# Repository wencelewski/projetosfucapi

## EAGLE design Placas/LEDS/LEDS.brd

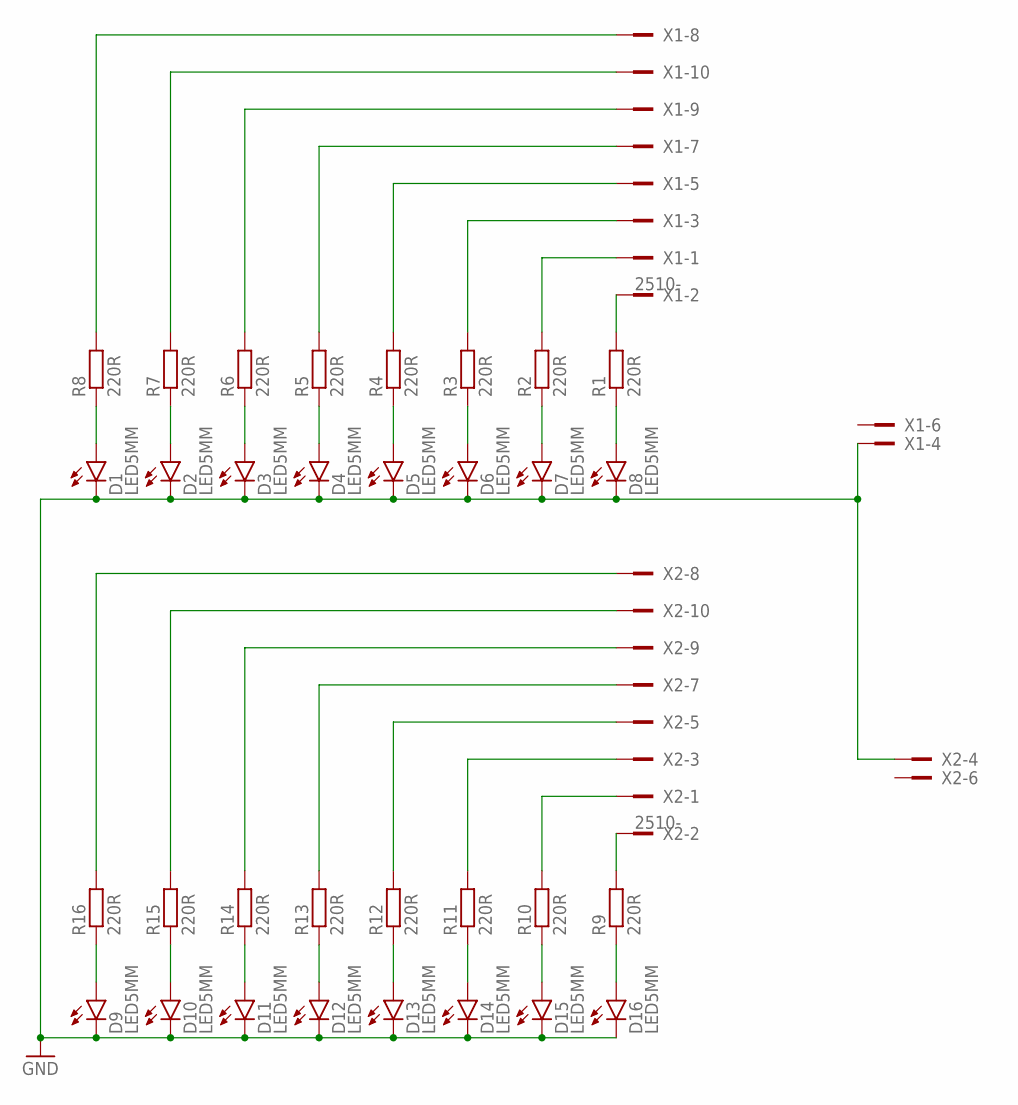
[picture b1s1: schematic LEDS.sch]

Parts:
D1, D2, D3, D4, D5, D6, D7, D8, D9, D10, D11, D12, D13, D14, D15, D16: LED5MM
R1, R2, R3, R4, R5, R6, R7, R8, R9, R10, R11, R12, R13, R14, R15, R16: 220R; 0204/ELVYS
X1, X2: 2510-; PAK100/2500-10

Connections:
GND: D1.K (C), D2.K (C), D3.K (C), D4.K (C), D5.K (C), D6.K (C), D7.K (C), D8.K (C), D9.K (C), D10.K (C), D11.K (C), D12.K (C), D13.K (C), D14.K (C), D15.K (C), D16.K (C), X1.4, X2.4
unnamed: R16.P$2 (2), X2.8
unnamed: R8.P$2 (2), X1.8
unnamed: R6.P$2 (2), X1.9
unnamed: R7.P$2 (2), X1.10
unnamed: R5.P$2 (2), X1.7
unnamed: R4.P$2 (2), X1.5
unnamed: R3.P$2 (2), X1.3
unnamed: R2.P$2 (2), X1.1
unnamed: R1.P$2 (2), X1.2
unnamed: R15.P$2 (2), X2.10
unnamed: R14.P$2 (2), X2.9
unnamed: R13.P$2 (2), X2.7
unnamed: R12.P$2 (2), X2.5
unnamed: R11.P$2 (2), X2.3
unnamed: R10.P$2 (2), X2.1
unnamed: R9.P$2 (2), X2.2
unnamed: D1.A, R8.P$1 (1)
unnamed: D2.A, R7.P$1 (1)
unnamed: D3.A, R6.P$1 (1)
unnamed: D4.A, R5.P$1 (1)
unnamed: D5.A, R4.P$1 (1)
unnamed: D6.A, R3.P$1 (1)
unnamed: D7.A, R2.P$1 (1)
unnamed: D8.A, R1.P$1 (1)
unnamed: D9.A, R16.P$1 (1)
unnamed: D10.A, R15.P$1 (1)
unnamed: D11.A, R14.P$1 (1)
unnamed: D12.A, R13.P$1 (1)
unnamed: D13.A, R12.P$1 (1)
unnamed: D14.A, R11.P$1 (1)
unnamed: D15.A, R10.P$1 (1)
unnamed: D16.A, R9.P$1 (1)

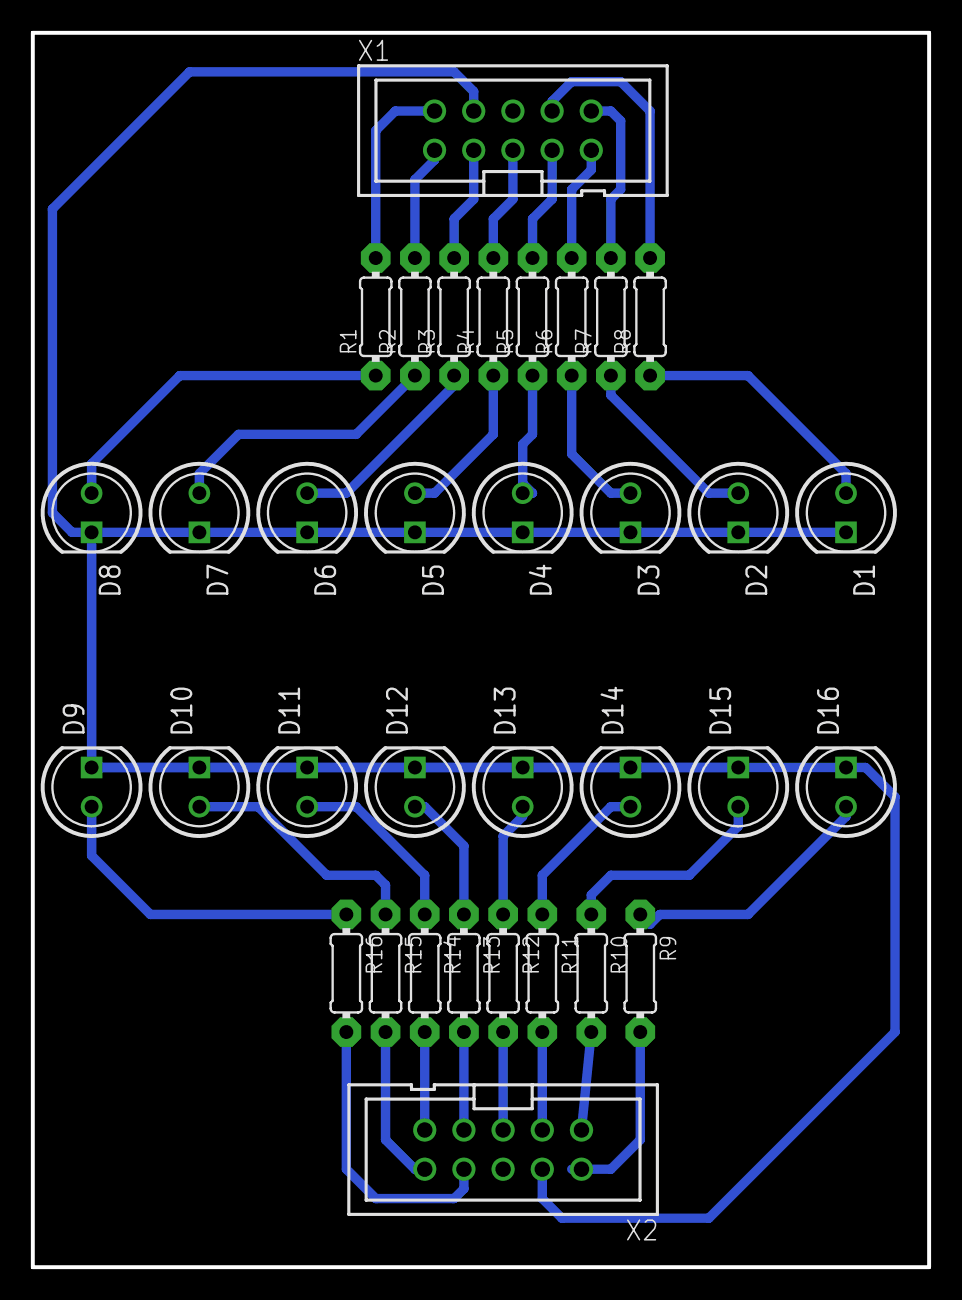
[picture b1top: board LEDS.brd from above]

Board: 2 copper layers, 58.1 x 80.0 mm, 34 parts (0 on the bottom side), 33 nets.

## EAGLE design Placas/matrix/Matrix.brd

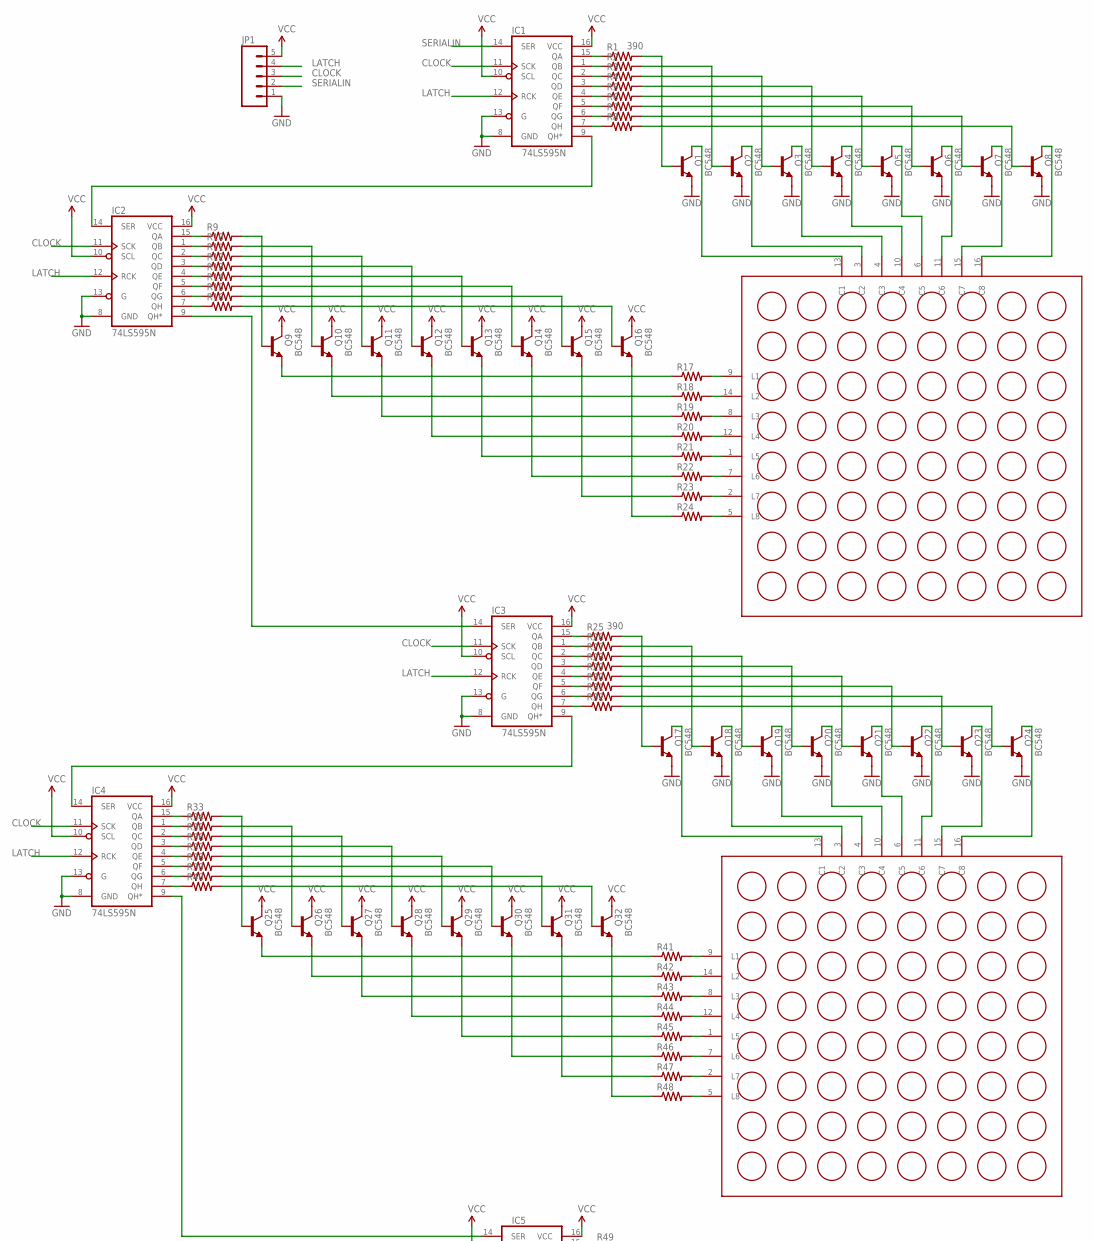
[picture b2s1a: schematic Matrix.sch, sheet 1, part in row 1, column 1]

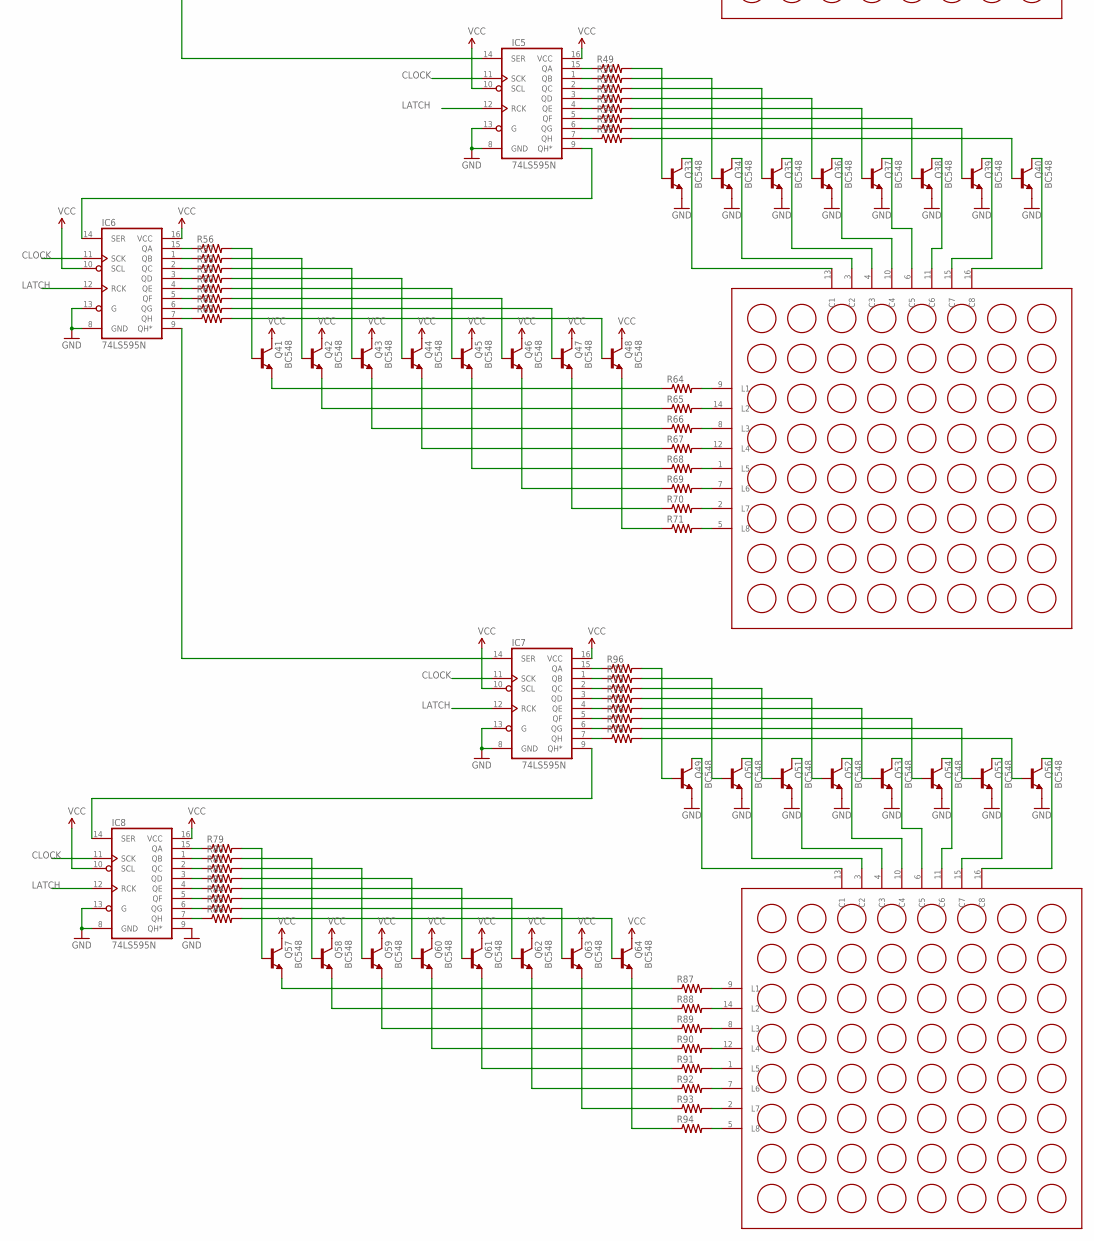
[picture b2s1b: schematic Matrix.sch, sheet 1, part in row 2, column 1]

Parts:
IC1, IC2, IC3, IC4, IC5, IC6, IC7, IC8: 74LS595N; DIL16
JP1: M05PTH_LONGPADS; 1X05_LONGPADS
Q1, Q2, Q3, Q4, Q5, Q6, Q7, Q8, Q9, Q10, Q11, Q12, Q13, Q14, Q15, Q16, Q17, Q18, Q19, Q20, Q21, Q22, Q23, Q24, Q25, Q26, Q27, Q28, Q29, Q30, Q31, Q32, Q33, Q34, Q35, Q36, Q37, Q38, Q39, Q40, Q41, Q42, Q43, Q44, Q45, Q46, Q47, Q48, Q49, Q50, Q51, Q52, Q53, Q54, Q55, Q56, Q57, Q58, Q59, Q60, Q61, Q62, Q63, Q64: BC548; TO92-EBC
R1, R2, R3, R4, R5, R6, R7, R8, R9, R10, R11, R12, R13, R14, R15, R16, R17, R18, R19, R20, R21, R22, R23, R24, R25, R26, R27, R28, R29, R30, R31, R32, R33, R34, R35, R36, R37, R38, R39, R40, R41, R42, R43, R44, R45, R46, R47, R48, R49, R50, R51, R52, R53, R54, R55, R56, R57, R58, R59, R60, R61, R62, R63, R64, R65, R66, R67, R68, R69, R70, R71, R72, R73, R74, R75, R76, R77, R78, R79, R80, R81, R82, R83, R84, R85, R86, R87, R88, R89, R90, R91, R92, R93, R94, R95, R96: 390; AXIAL-0.4
U$1, U$2, U$3, U$4: LEDMATRIX(HS2388); HS2388

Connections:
CLOCK: IC1.11 (SCK), IC2.11 (SCK), IC3.11 (SCK), IC4.11 (SCK), IC5.11 (SCK), IC6.11 (SCK), IC7.11 (SCK), IC8.11 (SCK), JP1.3
GND: IC1.8 (GND), IC1.13 (G), IC2.8 (GND), IC2.13 (G), IC3.8 (GND), IC3.13 (G), IC4.8 (GND), IC4.13 (G), IC5.8 (GND), IC5.13 (G), IC6.8 (GND), IC6.13 (G), IC7.8 (GND), IC7.13 (G), IC8.8 (GND), IC8.9 (QH*), IC8.13 (G), JP1.1, Q1.E, Q2.E, Q3.E, Q4.E, Q5.E, Q6.E, Q7.E, Q8.E, Q17.E, Q18.E, Q19.E, Q20.E, Q21.E, Q22.E, Q23.E, Q24.E, Q33.E, Q34.E, Q35.E, Q36.E, Q37.E, Q38.E, Q39.E, Q40.E, Q49.E, Q50.E, Q51.E, Q52.E, Q53.E, Q54.E, Q55.E, Q56.E
LATCH: IC1.12 (RCK), IC2.12 (RCK), IC3.12 (RCK), IC4.12 (RCK), IC5.12 (RCK), IC6.12 (RCK), IC7.12 (RCK), IC8.12 (RCK), JP1.4
unnamed: Q1.B, R1.P$2 (2)
unnamed: IC1.15 (QA), R1.P$1 (1)
unnamed: Q8.B, R8.P$2 (2)
unnamed: IC1.1 (QB), R2.P$1 (1)
unnamed: Q16.E, R24.P$1 (1)
unnamed: Q15.E, R23.P$1 (1)
unnamed: Q14.E, R22.P$1 (1)
unnamed: IC1.2 (QC), R3.P$1 (1)
unnamed: IC1.3 (QD), R4.P$1 (1)
unnamed: IC1.4 (QE), R5.P$1 (1)
unnamed: IC1.5 (QF), R6.P$1 (1)
unnamed: IC1.6 (QG), R7.P$1 (1)
unnamed: IC1.7 (QH), R8.P$1 (1)
unnamed: Q13.E, R21.P$1 (1)
unnamed: Q2.B, R2.P$2 (2)
unnamed: Q4.B, R4.P$2 (2)
unnamed: Q5.B, R5.P$2 (2)
unnamed: Q6.B, R6.P$2 (2)
unnamed: Q7.B, R7.P$2 (2)
unnamed: Q1.C, U$1.13 (C1)
unnamed: Q2.C, U$1.3 (C2)
unnamed: Q3.B, R3.P$2 (2)
unnamed: Q24.B, R32.P$2 (2)
unnamed: Q4.C, U$1.10 (C4)
unnamed: Q5.C, U$1.6 (C5)
unnamed: Q6.C, U$1.11 (C6)
unnamed: Q7.C, U$1.15 (C7)
unnamed: Q8.C, U$1.16 (C8)
unnamed: Q12.E, R20.P$1 (1)
unnamed: Q11.E, R19.P$1 (1)
unnamed: Q10.E, R18.P$1 (1)
unnamed: Q9.E, R17.P$1 (1)
unnamed: R17.P$2 (2), U$1.9 (L1)
unnamed: R18.P$2 (2), U$1.14 (L2)
unnamed: R19.P$2 (2), U$1.8 (L3)
unnamed: R20.P$2 (2), U$1.12 (L4)
unnamed: R21.P$2 (2), U$1.1 (L5)
unnamed: R22.P$2 (2), U$1.7 (L6)
unnamed: R23.P$2 (2), U$1.2 (L7)
unnamed: R24.P$2 (2), U$1.5 (L8)
unnamed: Q9.B, R9.P$2 (2)
unnamed: Q10.B, R10.P$2 (2)
unnamed: Q11.B, R11.P$2 (2)
unnamed: Q12.B, R12.P$2 (2)
unnamed: Q13.B, R13.P$2 (2)
unnamed: Q14.B, R14.P$2 (2)
unnamed: Q15.B, R15.P$2 (2)
unnamed: Q16.B, R16.P$2 (2)
unnamed: IC2.15 (QA), R9.P$1 (1)
unnamed: IC2.1 (QB), R10.P$1 (1)
unnamed: IC2.2 (QC), R11.P$1 (1)
unnamed: IC2.3 (QD), R12.P$1 (1)
unnamed: IC2.4 (QE), R13.P$1 (1)
unnamed: IC2.5 (QF), R14.P$1 (1)
unnamed: IC2.6 (QG), R15.P$1 (1)
unnamed: IC2.7 (QH), R16.P$1 (1)
unnamed: IC1.9 (QH*), IC2.14 (SER)
unnamed: Q19.B, R27.P$2 (2)
unnamed: Q3.C, U$1.4 (C3)
unnamed: Q17.B, R25.P$2 (2)
unnamed: Q18.B, R26.P$2 (2)
unnamed: Q20.B, R28.P$2 (2)
unnamed: Q21.B, R29.P$2 (2)
unnamed: Q22.B, R30.P$2 (2)
unnamed: Q23.B, R31.P$2 (2)
unnamed: Q17.C, U$2.13 (C1)
unnamed: Q18.C, U$2.3 (C2)
unnamed: Q20.C, U$2.10 (C4)
unnamed: Q21.C, U$2.6 (C5)
unnamed: Q22.C, U$2.11 (C6)
unnamed: Q23.C, U$2.15 (C7)
unnamed: Q24.C, U$2.16 (C8)
unnamed: IC3.15 (QA), R25.P$1 (1)
unnamed: IC3.1 (QB), R26.P$1 (1)
unnamed: IC3.2 (QC), R27.P$1 (1)
unnamed: IC3.3 (QD), R28.P$1 (1)
unnamed: IC3.4 (QE), R29.P$1 (1)
unnamed: IC3.5 (QF), R30.P$1 (1)
unnamed: IC3.6 (QG), R31.P$1 (1)
unnamed: IC3.7 (QH), R32.P$1 (1)
unnamed: Q32.E, R48.P$1 (1)
unnamed: Q31.E, R47.P$1 (1)
unnamed: Q30.E, R46.P$1 (1)
unnamed: Q29.E, R45.P$1 (1)
unnamed: Q28.E, R44.P$1 (1)
unnamed: Q27.E, R43.P$1 (1)
unnamed: Q26.E, R42.P$1 (1)
unnamed: Q25.E, R41.P$1 (1)
unnamed: R41.P$2 (2), U$2.9 (L1)
unnamed: R42.P$2 (2), U$2.14 (L2)
unnamed: R43.P$2 (2), U$2.8 (L3)
unnamed: R44.P$2 (2), U$2.12 (L4)
unnamed: R45.P$2 (2), U$2.1 (L5)
unnamed: R46.P$2 (2), U$2.7 (L6)
unnamed: R47.P$2 (2), U$2.2 (L7)
unnamed: R48.P$2 (2), U$2.5 (L8)
unnamed: Q25.B, R33.P$2 (2)
unnamed: Q26.B, R34.P$2 (2)
unnamed: Q27.B, R35.P$2 (2)
unnamed: Q28.B, R36.P$2 (2)
unnamed: Q29.B, R37.P$2 (2)
unnamed: Q30.B, R38.P$2 (2)
unnamed: Q31.B, R39.P$2 (2)
unnamed: Q32.B, R40.P$2 (2)
unnamed: IC4.15 (QA), R33.P$1 (1)
unnamed: IC4.1 (QB), R34.P$1 (1)
unnamed: IC4.2 (QC), R35.P$1 (1)
unnamed: IC4.3 (QD), R36.P$1 (1)
unnamed: IC4.4 (QE), R37.P$1 (1)
unnamed: IC4.5 (QF), R38.P$1 (1)
unnamed: IC4.6 (QG), R39.P$1 (1)
unnamed: IC4.7 (QH), R40.P$1 (1)
unnamed: Q19.C, U$2.4 (C3)
unnamed: IC3.9 (QH*), IC4.14 (SER)
unnamed: Q40.B, R95.P$2 (2)
unnamed: Q35.B, R51.P$2 (2)
unnamed: IC2.9 (QH*), IC3.14 (SER)
unnamed: Q34.B, R50.P$2 (2)
unnamed: Q36.B, R52.P$2 (2)
unnamed: Q37.B, R53.P$2 (2)
unnamed: Q38.B, R54.P$2 (2)
unnamed: Q39.B, R55.P$2 (2)
unnamed: Q33.C, U$3.13 (C1)
unnamed: Q34.C, U$3.3 (C2)
unnamed: Q36.C, U$3.10 (C4)
unnamed: Q37.C, U$3.6 (C5)
unnamed: Q38.C, U$3.11 (C6)
unnamed: Q39.C, U$3.15 (C7)
unnamed: Q40.C, U$3.16 (C8)
unnamed: Q33.B, R49.P$2 (2)
unnamed: IC6.9 (QH*), IC7.14 (SER)
unnamed: IC5.7 (QH), R95.P$1 (1)
unnamed: IC5.6 (QG), R55.P$1 (1)
unnamed: IC5.5 (QF), R54.P$1 (1)
unnamed: IC5.4 (QE), R53.P$1 (1)
unnamed: IC5.3 (QD), R52.P$1 (1)
unnamed: Q48.E, R71.P$1 (1)
unnamed: Q47.E, R70.P$1 (1)
unnamed: Q46.E, R69.P$1 (1)
unnamed: Q45.E, R68.P$1 (1)
unnamed: Q44.E, R67.P$1 (1)
unnamed: Q43.E, R66.P$1 (1)
unnamed: Q42.E, R65.P$1 (1)
unnamed: Q41.E, R64.P$1 (1)
unnamed: R64.P$2 (2), U$3.9 (L1)
unnamed: R65.P$2 (2), U$3.14 (L2)
unnamed: R66.P$2 (2), U$3.8 (L3)
unnamed: R67.P$2 (2), U$3.12 (L4)
unnamed: R68.P$2 (2), U$3.1 (L5)
unnamed: R69.P$2 (2), U$3.7 (L6)
unnamed: R70.P$2 (2), U$3.2 (L7)
unnamed: R71.P$2 (2), U$3.5 (L8)
unnamed: Q41.B, R56.P$2 (2)
unnamed: Q42.B, R57.P$2 (2)
unnamed: Q43.B, R58.P$2 (2)
unnamed: Q44.B, R59.P$2 (2)
unnamed: Q45.B, R60.P$2 (2)
unnamed: Q46.B, R61.P$2 (2)
unnamed: Q47.B, R62.P$2 (2)
unnamed: Q48.B, R63.P$2 (2)
unnamed: IC6.15 (QA), R56.P$1 (1)
unnamed: IC6.1 (QB), R57.P$1 (1)
unnamed: IC6.2 (QC), R58.P$1 (1)
unnamed: IC6.3 (QD), R59.P$1 (1)
unnamed: IC6.4 (QE), R60.P$1 (1)
unnamed: IC6.5 (QF), R61.P$1 (1)
unnamed: IC6.6 (QG), R62.P$1 (1)
unnamed: IC6.7 (QH), R63.P$1 (1)
unnamed: Q35.C, U$3.4 (C3)
unnamed: IC5.9 (QH*), IC6.14 (SER)
unnamed: Q56.B, R78.P$2 (2)
unnamed: Q51.B, R73.P$2 (2)
unnamed: Q49.B, R96.P$2 (2)
unnamed: Q50.B, R72.P$2 (2)
unnamed: Q52.B, R74.P$2 (2)
unnamed: Q53.B, R75.P$2 (2)
unnamed: Q54.B, R76.P$2 (2)
unnamed: Q55.B, R77.P$2 (2)
unnamed: Q49.C, U$4.13 (C1)
unnamed: Q50.C, U$4.3 (C2)
unnamed: Q52.C, U$4.10 (C4)
unnamed: Q53.C, U$4.6 (C5)
unnamed: Q54.C, U$4.11 (C6)
unnamed: Q55.C, U$4.15 (C7)
unnamed: Q56.C, U$4.16 (C8)
unnamed: IC7.1 (QB), R72.P$1 (1)
unnamed: IC7.2 (QC), R73.P$1 (1)
unnamed: IC7.3 (QD), R74.P$1 (1)
unnamed: IC7.4 (QE), R75.P$1 (1)
unnamed: IC7.5 (QF), R76.P$1 (1)
unnamed: IC7.6 (QG), R77.P$1 (1)
unnamed: IC7.7 (QH), R78.P$1 (1)
unnamed: Q64.E, R94.P$1 (1)
unnamed: Q63.E, R93.P$1 (1)
unnamed: Q62.E, R92.P$1 (1)
unnamed: Q61.E, R91.P$1 (1)
unnamed: Q60.E, R90.P$1 (1)
unnamed: Q59.E, R89.P$1 (1)
unnamed: Q58.E, R88.P$1 (1)
unnamed: Q57.E, R87.P$1 (1)
unnamed: R87.P$2 (2), U$4.9 (L1)
unnamed: R88.P$2 (2), U$4.14 (L2)
unnamed: R89.P$2 (2), U$4.8 (L3)
unnamed: R90.P$2 (2), U$4.12 (L4)
unnamed: R91.P$2 (2), U$4.1 (L5)
unnamed: R92.P$2 (2), U$4.7 (L6)
unnamed: R93.P$2 (2), U$4.2 (L7)
unnamed: R94.P$2 (2), U$4.5 (L8)
unnamed: Q57.B, R79.P$2 (2)
unnamed: Q58.B, R80.P$2 (2)
unnamed: Q59.B, R81.P$2 (2)
unnamed: Q60.B, R82.P$2 (2)
unnamed: Q61.B, R83.P$2 (2)
unnamed: Q62.B, R84.P$2 (2)
unnamed: Q63.B, R85.P$2 (2)
unnamed: Q64.B, R86.P$2 (2)
unnamed: IC8.15 (QA), R79.P$1 (1)
unnamed: IC8.1 (QB), R80.P$1 (1)
unnamed: IC8.2 (QC), R81.P$1 (1)
unnamed: IC8.3 (QD), R82.P$1 (1)
unnamed: IC8.4 (QE), R83.P$1 (1)
unnamed: IC8.5 (QF), R84.P$1 (1)
unnamed: IC8.6 (QG), R85.P$1 (1)
unnamed: IC8.7 (QH), R86.P$1 (1)
unnamed: Q51.C, U$4.4 (C3)
unnamed: IC7.9 (QH*), IC8.14 (SER)
unnamed: IC4.9 (QH*), IC5.14 (SER)
unnamed: IC5.2 (QC), R51.P$1 (1)
unnamed: IC5.1 (QB), R50.P$1 (1)
unnamed: IC5.15 (QA), R49.P$1 (1)
unnamed: IC7.15 (QA), R96.P$1 (1)
SERIALIN: IC1.14 (SER), JP1.2
VCC: IC1.10 (SCL), IC1.16 (VCC), IC2.10 (SCL), IC2.16 (VCC), IC3.10 (SCL), IC3.16 (VCC), IC4.10 (SCL), IC4.16 (VCC), IC5.10 (SCL), IC5.16 (VCC), IC6.10 (SCL), IC6.16 (VCC), IC7.10 (SCL), IC7.16 (VCC), IC8.10 (SCL), IC8.16 (VCC), JP1.5, Q9.C, Q10.C, Q11.C, Q12.C, Q13.C, Q14.C, Q15.C, Q16.C, Q25.C, Q26.C, Q27.C, Q28.C, Q29.C, Q30.C, Q31.C, Q32.C, Q41.C, Q42.C, Q43.C, Q44.C, Q45.C, Q46.C, Q47.C, Q48.C, Q57.C, Q58.C, Q59.C, Q60.C, Q61.C, Q62.C, Q63.C, Q64.C

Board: 2 copper layers, 173 parts (0 on the bottom side), 236 nets, no tracks yet.

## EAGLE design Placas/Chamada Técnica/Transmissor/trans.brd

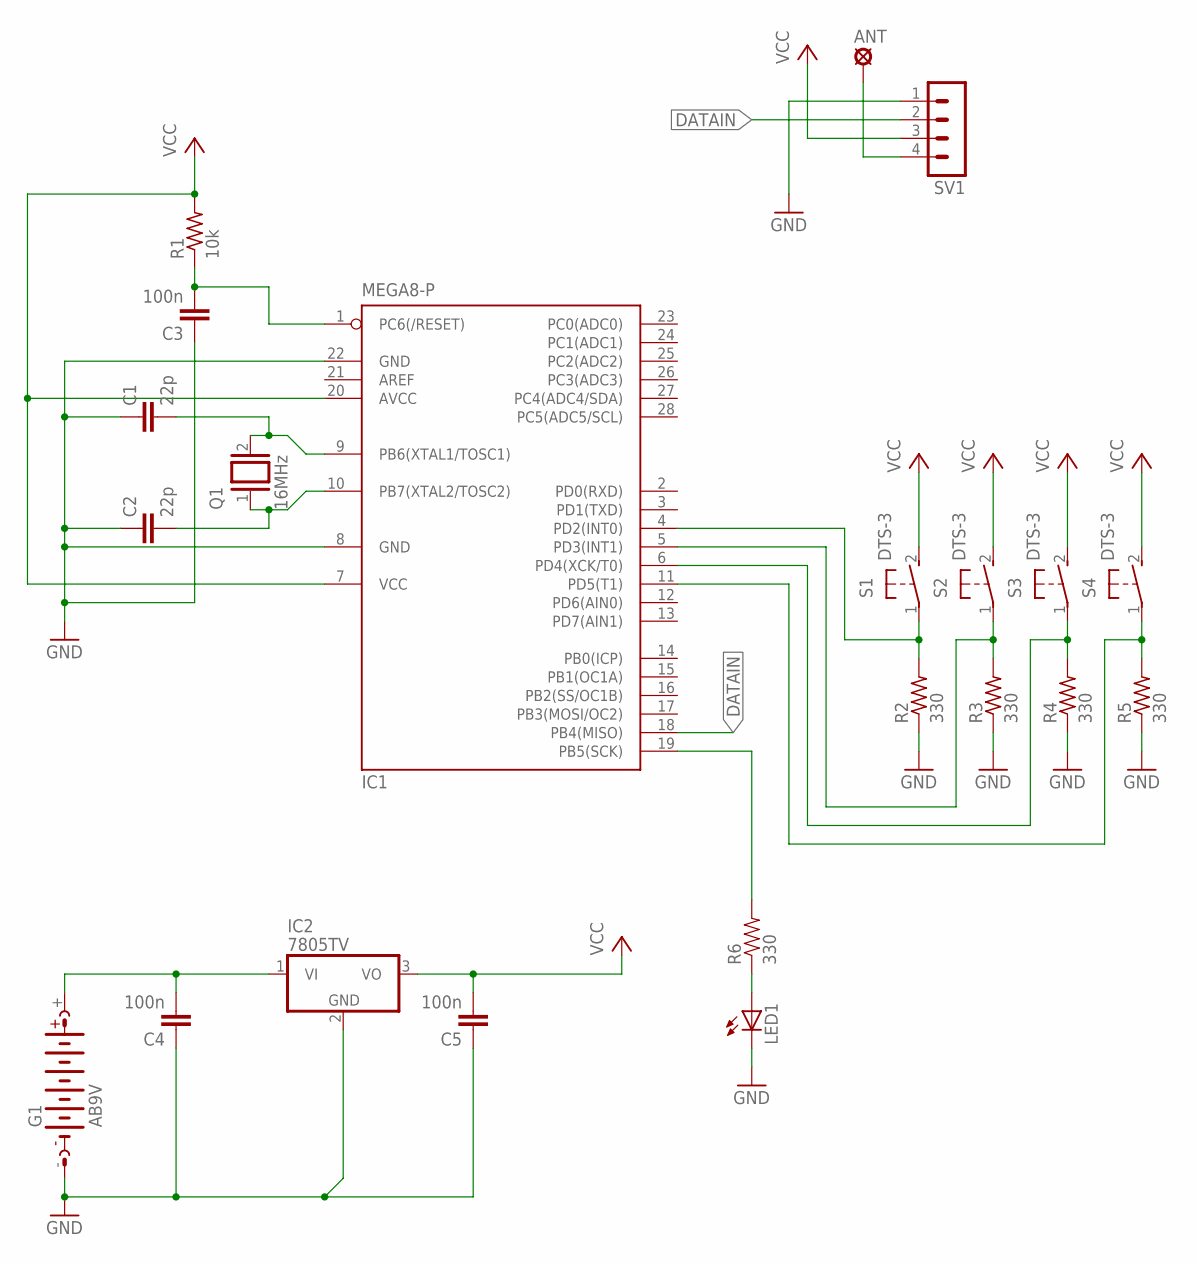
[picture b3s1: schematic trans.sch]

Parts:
ANT: LSP10
C1, C2: 22p; C025-024X044
C3, C4, C5: 100n; C025-024X044
G1: AB9V
IC1: MEGA8-P; DIL28-3
IC2: 7805TV; TO220V
LED1: LED5MM
Q1: 16MHz; QS
R1: 10k; 0204V
R2, R3, R4, R5: 330; 0204V
R6: 330; AXIAL-0.4
S1, S2, S3, S4: DTS-3
SV1: MA04-1

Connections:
DATAIN: IC1.18 (PB4(MISO)), SV1.2
GND: C1.1, C2.1, C3.1, C4.1, C5.1, G1.-, IC1.8 (GND), IC1.22 (GND), IC2.2 (GND), LED1.K (C), R2.1, R3.1, R4.1, R5.1, SV1.1
unnamed: C1.2, IC1.9 (PB6(XTAL1/TOSC1)), Q1.2
unnamed: C2.2, IC1.10 (PB7(XTAL2/TOSC2)), Q1.1
unnamed: C3.2, IC1.1 (PC6(/RESET)), R1.1
unnamed: ANT.MP, SV1.4
unnamed: C4.2, G1.+, IC2.1 (VI)
unnamed: IC1.4 (PD2(INT0)), R2.2, S1.1
unnamed: IC1.5 (PD3(INT1)), R3.2, S2.1
unnamed: IC1.19 (PB5(SCK)), R6.P$2 (2)
unnamed: IC1.11 (PD5(T1)), R5.2, S4.1
unnamed: IC1.6 (PD4(XCK/T0)), R4.2, S3.1
unnamed: LED1.A, R6.P$1 (1)
VCC: C5.2, IC1.7 (VCC), IC1.20 (AVCC), IC2.3 (VO), R1.2, S1.2, S2.2, S3.2, S4.2, SV1.3

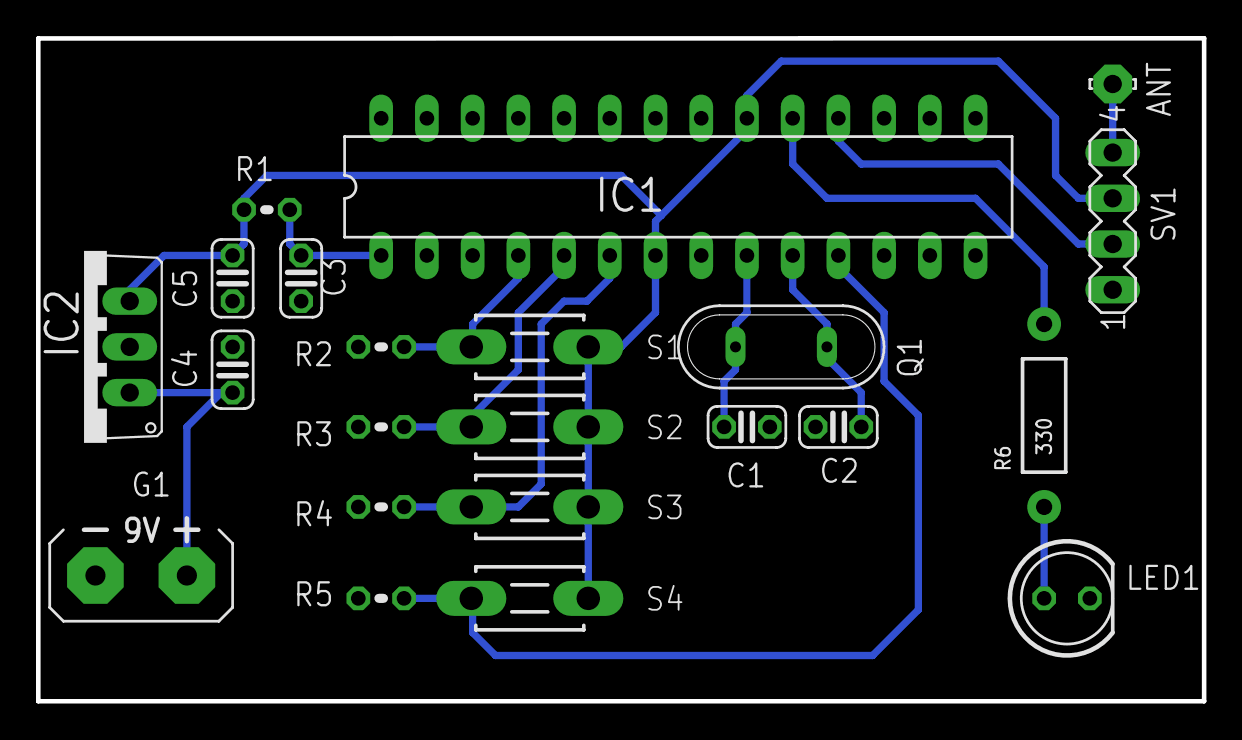
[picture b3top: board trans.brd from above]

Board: 2 copper layers, 64.8 x 36.8 mm, 22 parts (0 on the bottom side), 14 nets.

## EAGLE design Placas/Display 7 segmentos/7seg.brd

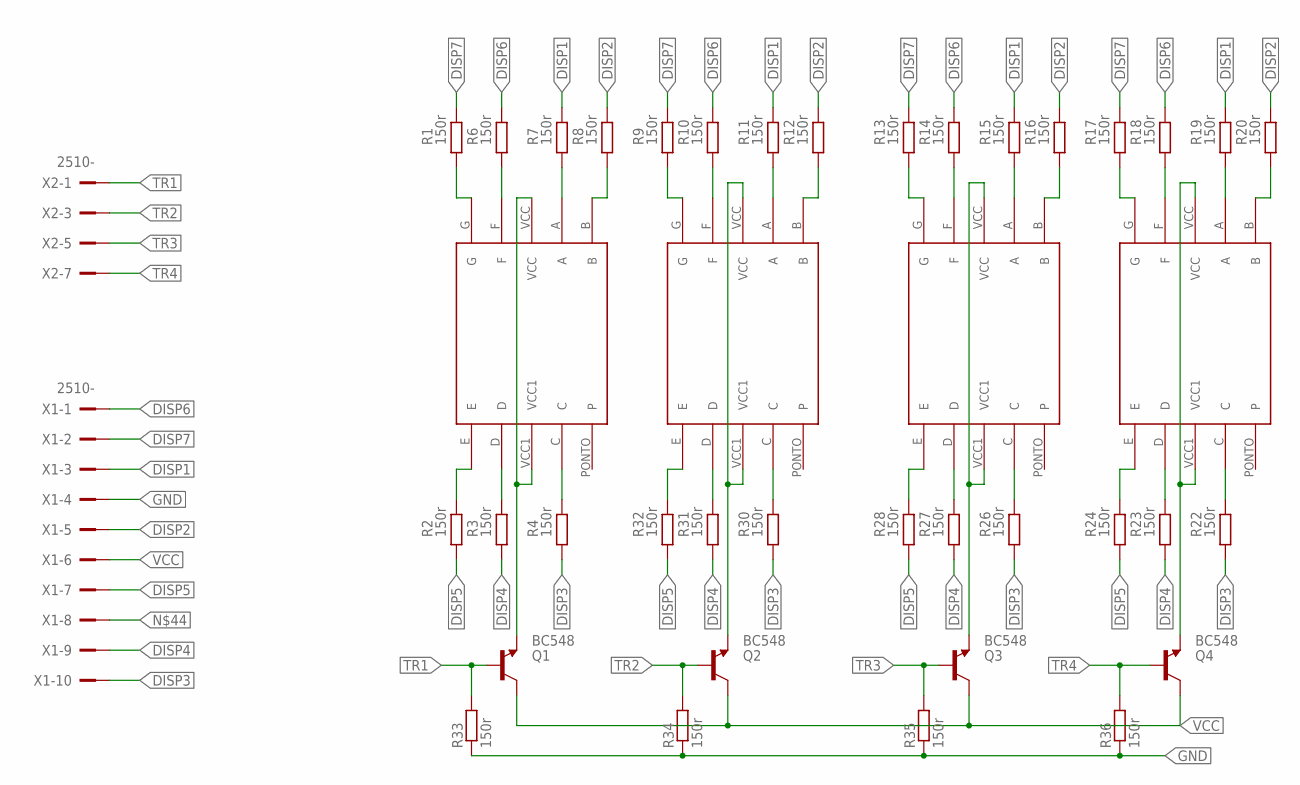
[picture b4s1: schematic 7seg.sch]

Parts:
Q1, Q2, Q3, Q4: BC548; TO92-EBC
R1, R2, R3, R4, R6, R7, R8, R9, R10, R11, R12, R13, R14, R15, R16, R17, R18, R19, R20, R22, R23, R24, R26, R27, R28, R30, R31, R32, R33, R34, R35, R36: 150r; 0204/ELVYS
U$1, U$2, U$3, U$4: HS-12101BS
X1, X2: 2510-; PAK100/2500-10

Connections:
DISP1: R7.P$2 (2), R11.P$2 (2), R15.P$2 (2), R19.P$2 (2), X1.3
DISP2: R8.P$2 (2), R12.P$2 (2), R16.P$2 (2), R20.P$2 (2), X1.5
DISP3: R4.P$1 (1), R22.P$1 (1), R26.P$1 (1), R30.P$1 (1), X1.10
DISP4: R3.P$1 (1), R23.P$1 (1), R27.P$1 (1), R31.P$1 (1), X1.9
DISP5: R2.P$1 (1), R24.P$1 (1), R28.P$1 (1), R32.P$1 (1), X1.7
DISP6: R6.P$2 (2), R10.P$2 (2), R14.P$2 (2), R18.P$2 (2), X1.1
DISP7: R1.P$2 (2), R9.P$2 (2), R13.P$2 (2), R17.P$2 (2), X1.2
GND: R33.P$1 (1), R34.P$1 (1), R35.P$1 (1), R36.P$1 (1), X1.4
unnamed: Q1.E, U$1.VCC, U$1.VCC1
unnamed: Q2.E, U$2.VCC, U$2.VCC1
unnamed: R1.P$1 (1), U$1.G
unnamed: R2.P$2 (2), U$1.E
unnamed: R4.P$2 (2), U$1.C
unnamed: R3.P$2 (2), U$1.D
unnamed: R6.P$1 (1), U$1.F
unnamed: R7.P$1 (1), U$1.A
unnamed: R8.P$1 (1), U$1.B
unnamed: R9.P$1 (1), U$2.G
unnamed: R10.P$1 (1), U$2.F
unnamed: R11.P$1 (1), U$2.A
unnamed: R12.P$1 (1), U$2.B
unnamed: R13.P$1 (1), U$3.G
unnamed: R14.P$1 (1), U$3.F
unnamed: R15.P$1 (1), U$3.A
unnamed: R16.P$1 (1), U$3.B
unnamed: R17.P$1 (1), U$4.G
unnamed: R18.P$1 (1), U$4.F
unnamed: R19.P$1 (1), U$4.A
unnamed: R20.P$1 (1), U$4.B
unnamed: R22.P$2 (2), U$4.C
unnamed: R23.P$2 (2), U$4.D
unnamed: R24.P$2 (2), U$4.E
unnamed: R26.P$2 (2), U$3.C
unnamed: R27.P$2 (2), U$3.D
unnamed: R28.P$2 (2), U$3.E
unnamed: R30.P$2 (2), U$2.C
unnamed: R31.P$2 (2), U$2.D
unnamed: R32.P$2 (2), U$2.E
unnamed: Q4.E, U$4.VCC, U$4.VCC1
unnamed: Q3.E, U$3.VCC, U$3.VCC1
TR1: Q1.B, R33.P$2 (2), X2.1
TR2: Q2.B, R34.P$2 (2), X2.3
TR3: Q3.B, R35.P$2 (2), X2.5
TR4: Q4.B, R36.P$2 (2), X2.7
VCC: Q1.C, Q2.C, Q3.C, Q4.C, X1.6

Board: 2 copper layers, 42 parts (0 on the bottom side), 45 nets, no tracks yet.

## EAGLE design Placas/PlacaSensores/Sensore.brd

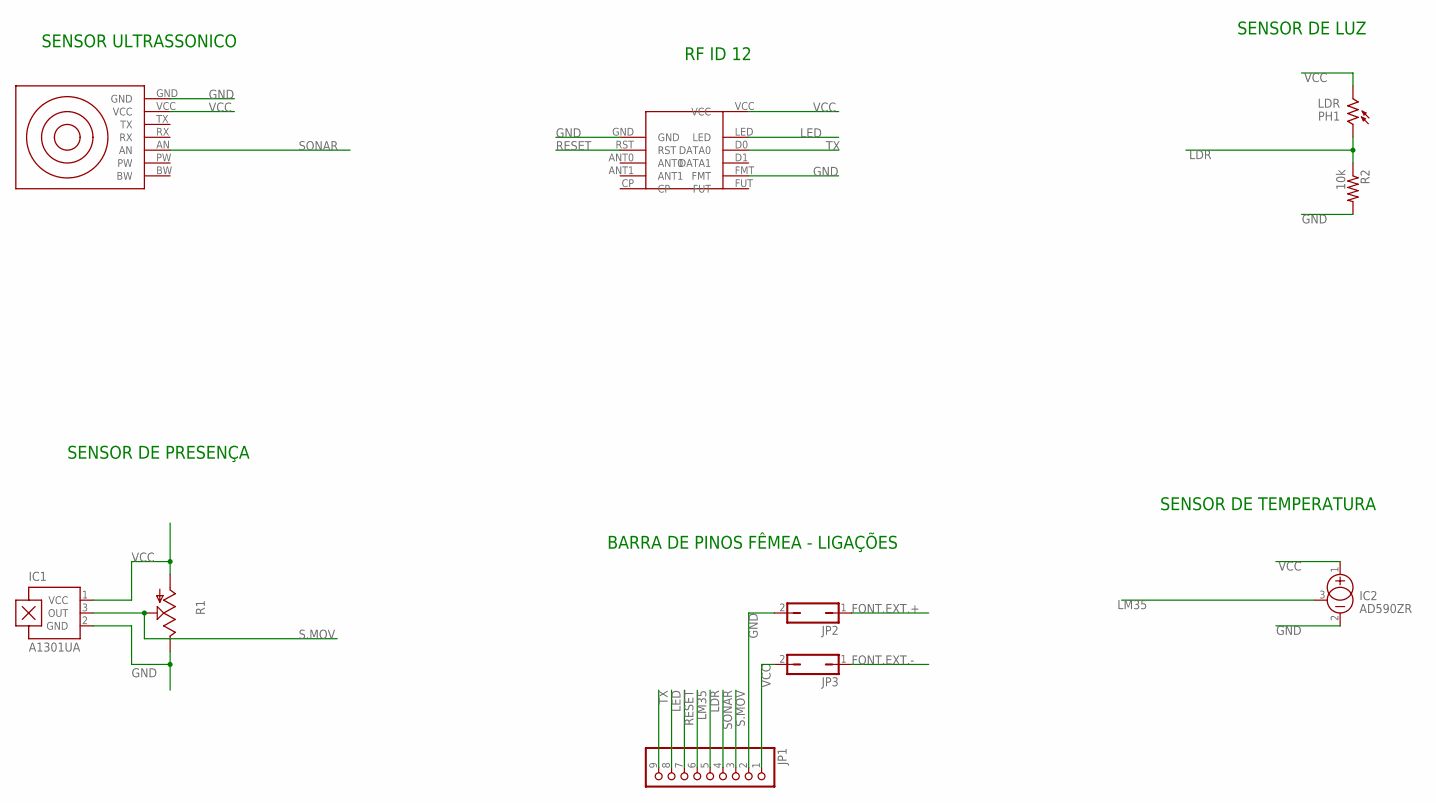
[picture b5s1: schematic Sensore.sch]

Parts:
IC1: A1301UA; SIP3-UA
IC2: AD590ZR; TO92
JP1: PINHD-1X9; 1X09
JP2, JP3: JP1Q; JP1
PH1: LDR; T0-46-A10XX
R1: TRIM_US-CIP20C-6MM; CIP20C-6MM
R2: 10k; 0207/10
U$1: LV-EZ1
U$2: RFID12

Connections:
FONT.EXT.+: JP2.1
FONT.EXT.-: JP3.1
GND: IC1.2 (GND), IC2.2 (-), JP1.2, JP2.2, R1.E, R2.2, U$1.GND, U$2.FMT, U$2.GND
LDR: JP1.5, PH1.1, R2.1
LED: JP1.8, U$2.LED
LM35: IC2.3 (CAN), JP1.6
RESET: JP1.7, U$2.RST
S.MOV: IC1.3 (OUT), JP1.3, R1.S
SONAR: JP1.4, U$1.AN
TX: JP1.9, U$2.D0 (DATA0)
VCC: IC1.1 (VCC), IC2.1 (+), JP1.1, JP3.2, PH1.2, R1.A, U$1.VCC, U$2.VCC

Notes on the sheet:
SENSOR DE TEMPERATURA
SENSOR DE LUZ
SENSOR DE PRESENÇA
SENSOR ULTRASSONICO
RF ID 12
BARRA DE PINOS FÊMEA - LIGAÇÕES

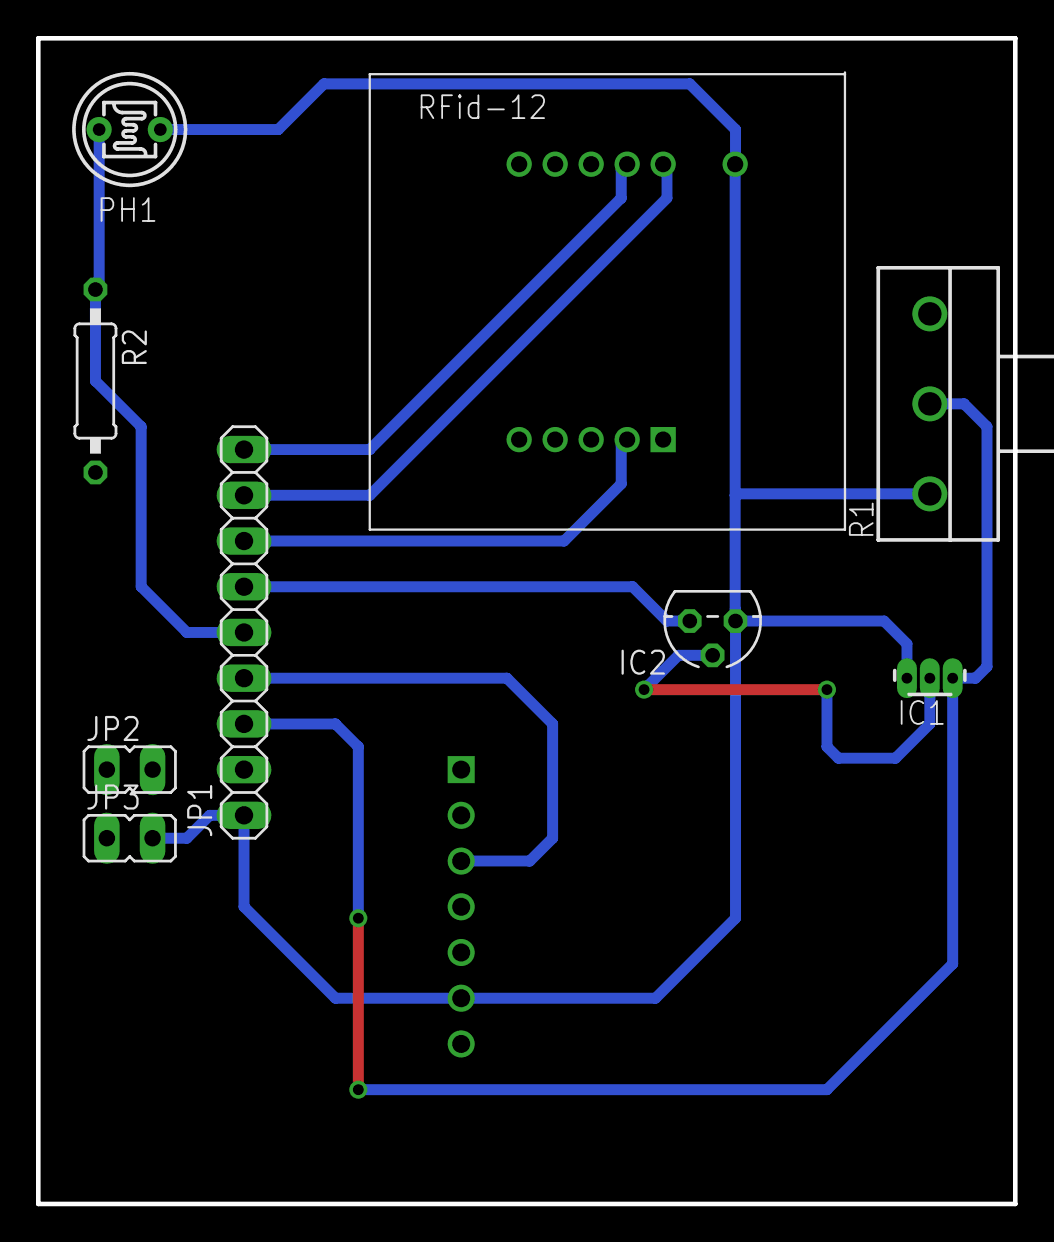
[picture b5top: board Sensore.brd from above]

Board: 2 copper layers, 54.3 x 64.8 mm, 10 parts (0 on the bottom side), 9 nets.

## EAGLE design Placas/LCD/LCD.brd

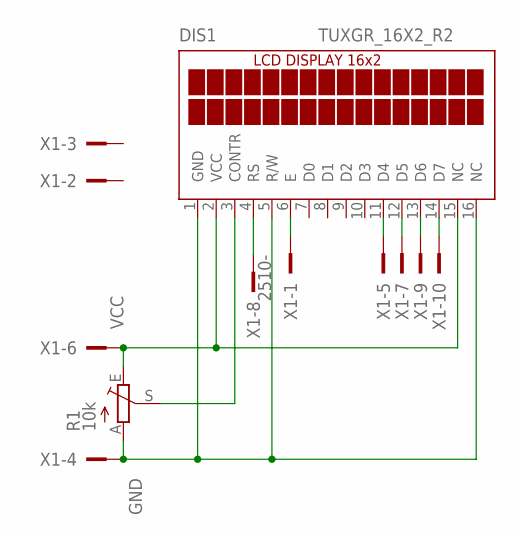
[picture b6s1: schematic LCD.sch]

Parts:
DIS1: TUXGR_16X2_R2
R1: 10k; RS3
X1: 2510-; PAK100/2500-10

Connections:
GND: DIS1.1 (GND), DIS1.5 (R/W), DIS1.16 (NC), R1.A, X1.4
unnamed: DIS1.13 (D6), X1.9
unnamed: DIS1.14 (D7), X1.10
unnamed: DIS1.11 (D4), X1.5
unnamed: DIS1.12 (D5), X1.7
unnamed: DIS1.4 (RS), X1.8
unnamed: DIS1.3 (CONTR), R1.S
unnamed: DIS1.6 (E), X1.1
VCC: DIS1.2 (VCC), DIS1.15 (NC), R1.E, X1.6

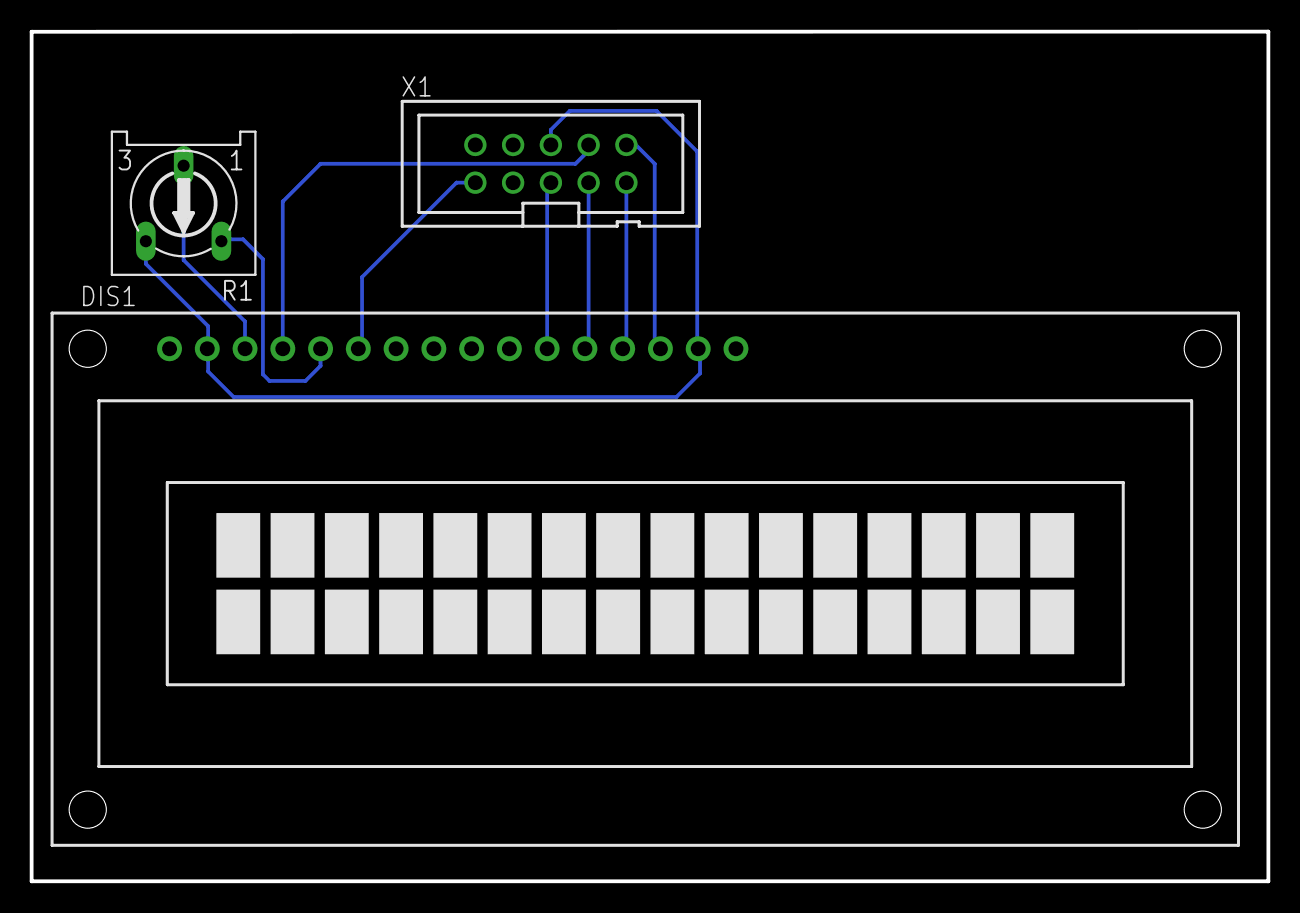
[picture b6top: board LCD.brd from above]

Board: 2 copper layers, 83.2 x 57.1 mm, 3 parts (0 on the bottom side), 9 nets.

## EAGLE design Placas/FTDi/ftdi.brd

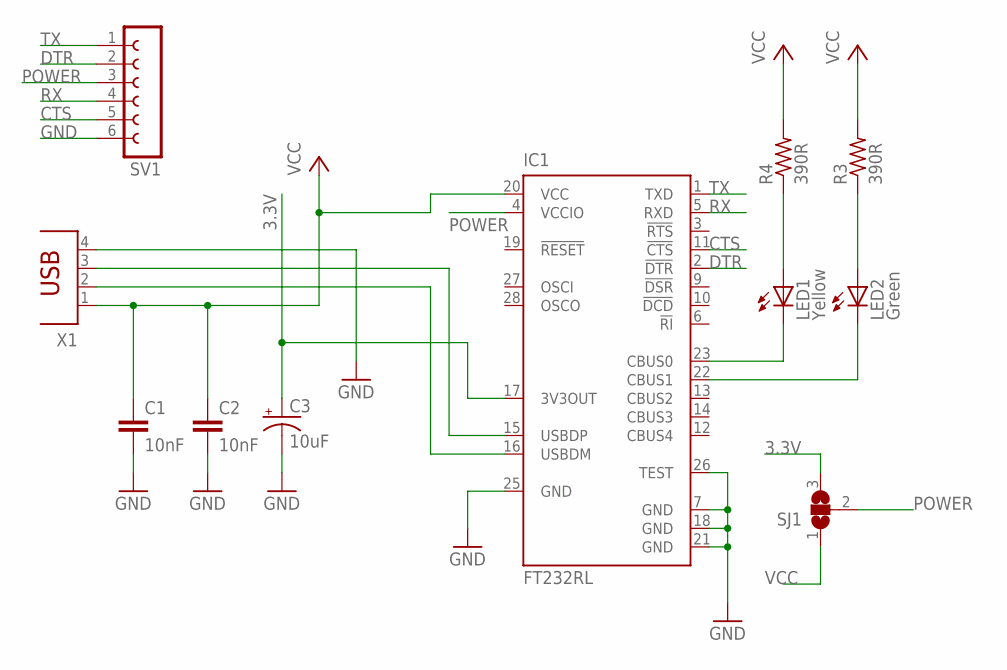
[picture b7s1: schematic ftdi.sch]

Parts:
C1, C2: 10nF; C0805
C3: 10uF; E2,5-6
IC1: FT232RL; SSOP28
LED1: Yellow; LED5MM
LED2: Green; LED5MM
R3, R4: 390R; R0805
SJ1: SJ2W; SJ_2
SV1: FE06-1; FE06
X1: PN87520

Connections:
3.3V: C3.+, IC1.17 (3V3OUT), SJ1.3
CTS: IC1.11 (!CTS), SV1.5
DTR: IC1.2 (!DTR), SV1.2
GND: C1.2, C2.2, C3.-, IC1.7 (GND), IC1.18 (GND), IC1.21 (GND), IC1.25 (GND), IC1.26 (TEST), SV1.6, X1.4
unnamed: IC1.23 (CBUS0), LED1.K (C)
unnamed: IC1.22 (CBUS1), LED2.K (C)
unnamed: LED2.A, R3.1
unnamed: LED1.A, R4.1
unnamed: IC1.16 (USBDM), X1.2
unnamed: IC1.15 (USBDP), X1.3
POWER: IC1.4 (VCCIO), SJ1.2, SV1.3
RX: IC1.5 (RXD), SV1.4
TX: IC1.1 (TXD), SV1.1
VCC: C1.1, C2.1, IC1.20 (VCC), R3.2, R4.2, SJ1.1, X1.1

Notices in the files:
parts and their libraries:
SparkFun: Licensing: CC v3.0 Share-Alike You are welcome to use this library for commercial purposes.
